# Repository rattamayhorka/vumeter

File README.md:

# Vumeter - Tablero con Control de Volumen y Display OLED multimedia 

Vumeter, es un proyecto con el que puedes mostrar en un OLED, información en tiempo real como Artista y Cancíón que se está reproduciendo en Linux, muy parecido a lo que era LCD Smartie, :D

Este script de Python interactúa con reproductores multimedia a traves de D-Bus y formatea la información y la envía al atmega32 que controla la pantalla OLED.

## Por implementar:

- vumetro (30%)
- notificaciónes (0%)

## Software

- [Python 3.x](https://www.python.org/downloads/)
- [Daemonize](https://pypi.org/project/daemonize/)
- [pydbus](https://pypi.org/project/pydbus/)
- [unidecode](https://pypi.org/project/Unidecode/)
- [pamixer](https://man.archlinux.org/man/pamixer.1)
- [playerctld](https://archlinux.org/packages/extra/x86_64/playerctl/)

## Hardware

- NEW-HEAVEN OLED DISPLAY [NHD-0420CW OLED SLIM DISPLAY] (https://newhavendisplay.com/content/specs/NHD-0420CW-AY3.pdf)
- MICROCHIP ATMEGA-32 MICROCONTROLLER [ATMEGA32](https://ww1.microchip.com/downloads/en/DeviceDoc/doc2503.pdf)
- USB SERIAL CONVERTER [USB - SERIAL TTL ](https://www.tostatronic.com/product/convertidor-ttl-pl2303-usb-to-rs232-ttl-converter/?gad_source=1&gclid=Cj0KCQiA67CrBhC1ARIsACKAa8TZjBnonuWXY4yLTC7wkeTdMWY1l-ocxSXjfy_Q063HC-wARc6UHUAaAhSuEALw_wcB)

## Conexiones: 

#define SCL PB6  
#define SDI PB5  
#define CS PB1  

## Serial interface NHD-0420CW configuration:
BS0 - GND  
BS1 - GND  
BS2 - GND  

## OLED CONNECTIONS  PCB / ATMEGA CONNECTIONS   
1  - VSS              GND  
2  - VDD              VOLTAGE  
3  - REGVDD           VOLTAGE  
4  - D/C              GND  
5  - R/W              GND  
6  - E                GND  
7  - D0 [SCLK]        PB6  
8  - D1 [SDI]         PB5  
9  - D2               GND  
10 - D3               GND  
11 - D4               GND  
12 - D5               GND  
13 - D6               GND  
14 - D7               GND  
15 - CS               PB1  
16 - RES              VOLTAGE  
17 - BS0 [SERIAL]     GND  
18 - BS1 [SERIAL]     GND  
19 - BS2 [SERIAL]     GND  
20 - VSS(FRAMEGROUND) GND

## ENCODER CONNECTIONS / ATMEGA CONNECTIONS   
1  - GND              GND  
2  - VCC              VOLTAGE  
3  - SW               PD4  
4  - DT               PD3  
5  - CLK              PD2  

## Diagrama 

## PCB 

## 3D image 

## Configuración

Asegúrate de tener todos los requisitos instalados antes de ejecutar el script.

```bash
pip install pydbus unidecode
```
## Uso

Ejecuta el script de la siguiente manera:

```bash
python dbus_data_tx.py
```

El script detectará reproductores multimedia activos y mostrará información sobre la canción en el display OLED. También permite ajustar el volumen mediante un convertidor usb-serial conectado al microcontrolador.

## Notas

- Asegúrate de tener permisos para acceder al puerto serie (`/dev/ttyUSB0` en este caso).
- Ajusta el puerto serie y el baudrate según tu configuración.

## Contribuciones

¡Contribuciones son bienvenidas! Si encuentras errores o mejoras posibles, no dudes en crear un *issue* o enviar un *pull request*.

## Autor

[rattamayhorka]

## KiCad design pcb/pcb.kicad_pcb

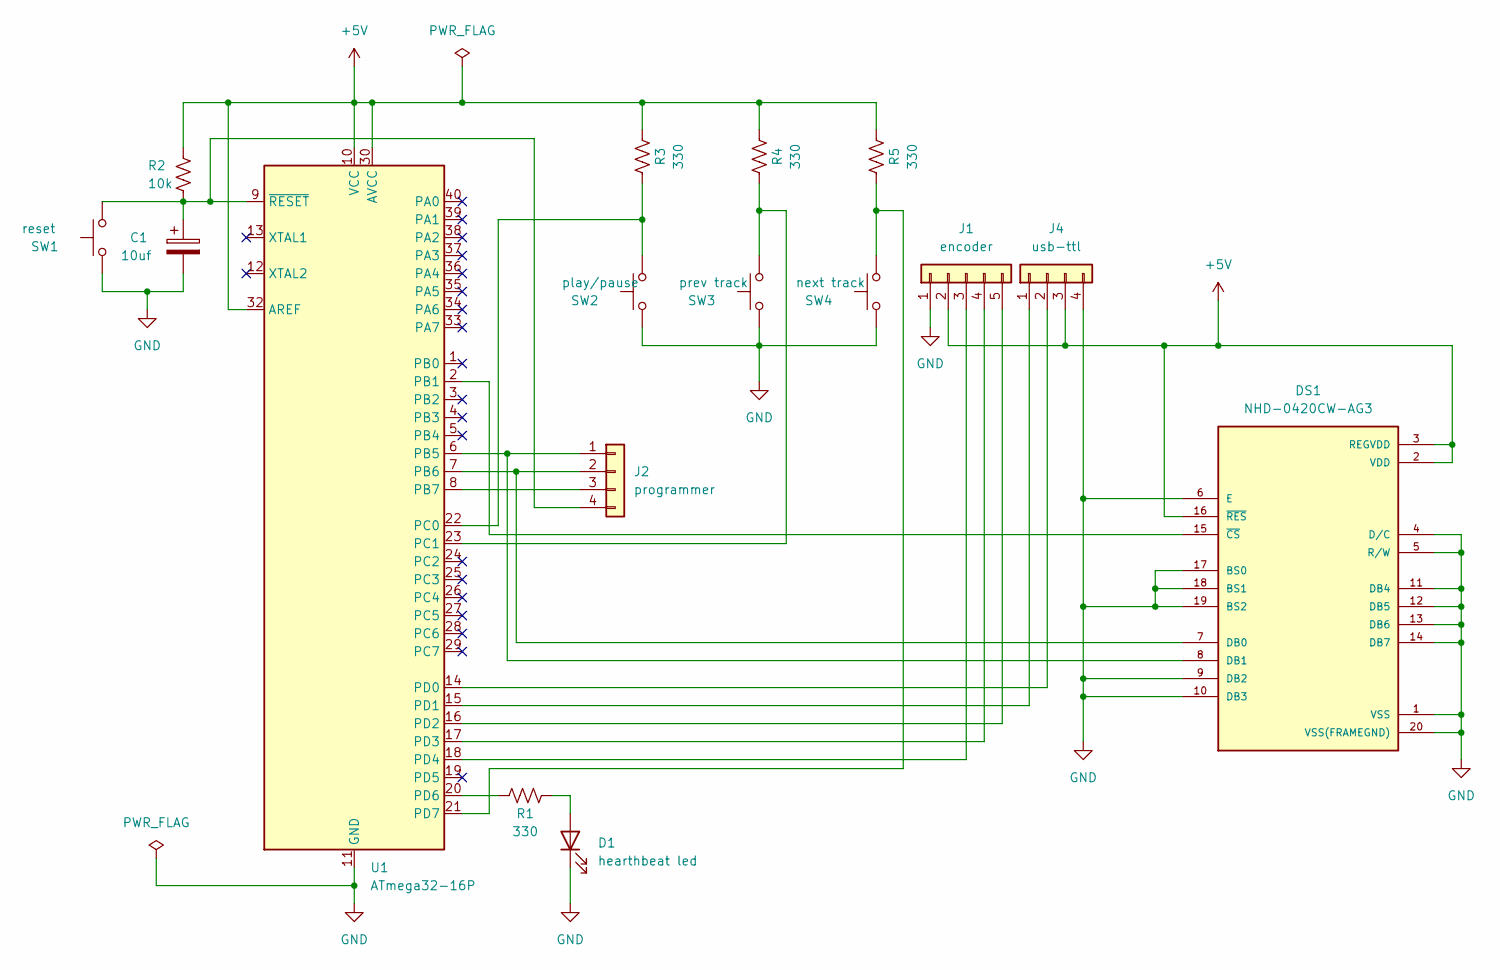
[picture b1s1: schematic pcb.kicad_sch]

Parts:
C1: 10uf; CP_Radial_D5.0mm_P2.00mm
D1: hearthbeat led; LED_D5.0mm
DS1: NHD-0420CW-AG3; NHD_NHD-0420CW-AG3
J1: encoder
J2: programmer; PinHeader_1x04_P2.54mm_Vertical
J4: usb-ttl; PinHeader_1x04_P2.54mm_Vertical
R1, R3, R4, R5: 330; R_Axial_DIN0207_L6.3mm_D2.5mm_P7.62mm_Horizontal
R2: 10k; R_Axial_DIN0207_L6.3mm_D2.5mm_P7.62mm_Horizontal
SW1: reset; SW_PUSH_6mm
SW2: play/pause; SW_PUSH_6mm
SW3: prev track; SW_PUSH_6mm
SW4: next track; SW_PUSH_6mm
U1: ATmega32-16P; DIP-40_W15.24mm

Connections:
+5V: DS1.2 (VDD), DS1.3 (REGVDD), DS1.16 (~RES), J1.2, J4.3, R2.2, R3.2, R4.2, R5.2, U1.10 (VCC), U1.30 (AVCC), U1.32 (AREF)
GND: C1.2, D1.1 (K), DS1.1 (VSS), DS1.4 (D/C), DS1.5 (R/W), DS1.6 (E), DS1.9 (DB2), DS1.10 (DB3), DS1.11 (DB4), DS1.12 (DB5), DS1.13 (DB6), DS1.14 (DB7), DS1.17 (BS0), DS1.18 (BS1), DS1.19 (BS2), DS1.20 (VSS(FRAMEGND)), J1.1, J4.4, SW1.1, SW2.1, SW3.1, SW4.1, U1.11 (GND), U1.31 (GND)
unnamed: D1.2 (A), R1.2
unnamed: DS1.7 (DB0), J2.2, U1.7 (PB6)
unnamed: DS1.8 (DB1), J2.1, U1.6 (PB5)
unnamed: DS1.15 (~CS), U1.2 (PB1)
unnamed: J1.3, U1.18 (PD4)
unnamed: J1.4, U1.17 (PD3)
unnamed: J1.5, U1.16 (PD2)
unnamed: J2.3, U1.8 (PB7)
unnamed: C1.1, J2.4, R2.1, SW1.2, U1.9 (~RESET)
unnamed: J4.1, U1.15 (PD1)
unnamed: J4.2, U1.14 (PD0)
unnamed: R3.1, SW2.2, U1.22 (PC0)
unnamed: R4.1, SW3.2, U1.23 (PC1)
unnamed: R1.1, U1.20 (PD6)
unnamed: R5.1, SW4.2, U1.21 (PD7)

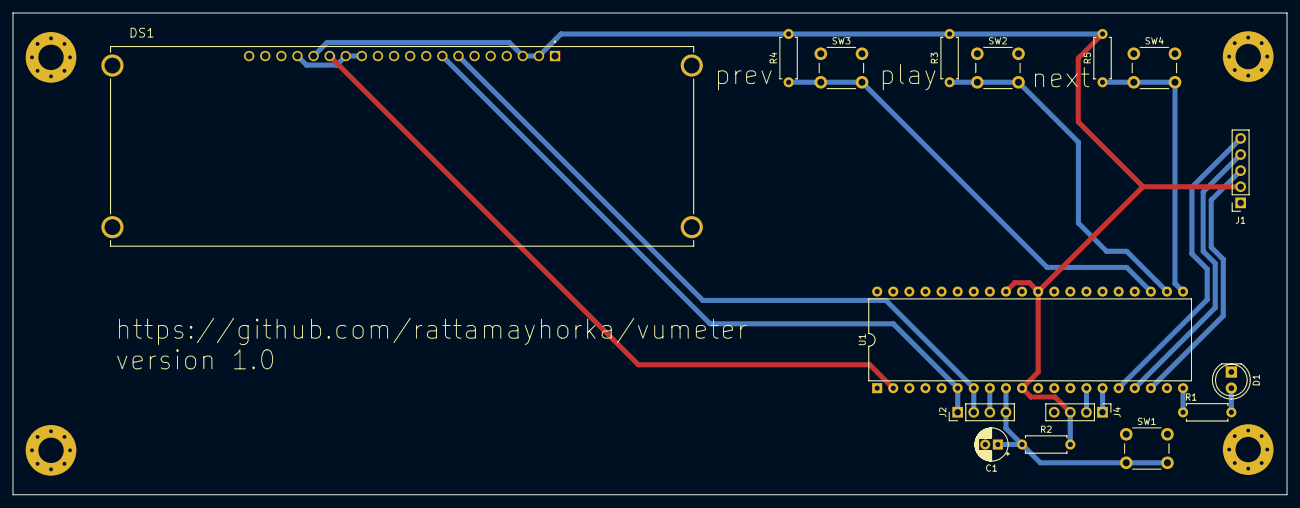
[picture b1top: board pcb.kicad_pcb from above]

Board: 2 copper layers, 201.0 x 76.0 mm, 16 parts (0 on the bottom side), 17 nets.

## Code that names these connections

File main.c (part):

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int aLastState_1;

int read_encoder(void){
    return ((PIND & (1 << PD2)) >> PD2) | (((PIND & (1 << PD3)) >> PD3) << 1);
}

void usart_init(void){
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    static uint16_t counter = 0;

    if (counter < 1) {
        PORTD |= (1 << PD6); // Enciende el LED
    } else {
        PORTD &= ~(1 << PD6); // Apaga el LED
    }

    counter++;
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}    

void ports_init(void){
    DDRB |= (1 << PB6) | (1 << PB5) | (1 << PB1); //configurar PB1 as CS, PB5 [oled 8] as SDI, pb6 as SCL [oled 7] 

    DDRD |= (1 << PD6); //configurar PD6 como salida LED heartbeat
        
    DDRC &= ~(1 << PD7); // botones multimedia (play)
    DDRC &= ~(1 << PC0); // botones multimedia (next)
    DDRC &= ~(1 << PC1); // botones multimedia (prev)

    DDRD &= ~(1 << PD4);  // PD4 como entrada (SW - encoder)
    DDRD &= ~(1 << PD3);  // PD3 como entrada (DT - encoder)
    DDRD &= ~(1 << PD2);  // PD2 como entrada (CLK - encoder)

    PORTD |= (1 << PD2) | (1 << PD3);  // Habilitar resistencias de pull-up
}

void boot(void){ //funcion de inicio
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    //boot_splash();
    usart_init(); // Inicializar USART    
    sei();
    PORTD |= (1 << PD6);    
}

int main(void){
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        }

        aLastState_1 = aState_1;
        if (!(PINC & (1 << PC0))) {
            if (switch_next == 0) {
                // El estado del interruptor ha cambiado a presionado
                char debug_message[20];
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            switch_next = 0;
        }

        if (!(PINC & (1 << PC1))) {
            if (switch_prev == 0) {
                // El estado del interruptor ha cambiado a presionado
                char debug_message[20];
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            switch_prev = 0;
        }

        if (!(PIND & (1 << PD4))) {
            if (switch_mute == 0) {
                // El estado del interruptor ha cambiado a presionado
                char debug_message[20];
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            switch_mute = 0;
        }

        if (!(PIND & (1 << PD7))) {
            if (switch_play == 0) {
                // El estado del interruptor ha cambiado a presionado
                char debug_message[20];
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
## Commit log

2023-08-20 inicio de proyecto
2023-08-23 previo a la implementación del ADC
2023-08-23 pruebas con barras y adc
2023-09-01 se actualiza el software para un lcd de 4 lineas y se corrigen caracteres
2023-09-04 modifico pines de lcd.h
2023-09-04 elimino warnings en read_adc
2023-09-05 agrego comunicacion avr@pc USART
2023-09-06 agrego los saltos de linea
2023-09-06 envío de caracteres con valor de ADC a python
2023-09-06 haciendo pruebas con control de volumen
2023-09-10 control analogico de volumen funcionando
2023-09-12 agrego opcion de salida de musica con cmus
2023-09-12 renombrar archivos
2023-09-14 separación de implementaciones
2023-09-14 limpiando versiones
2023-09-15 lcd originales de pfleury
2023-09-17 implementación de vector usart para la recepcion con interrupciones
2023-09-18 actualizando lista de archivos
2023-09-18 elimino decimales en volumen y lo envío solo si es diferente al valor enviado anterior
2023-09-20 transmision y recepcion en el mismo programa python
2023-09-21 ordenando y comentando codigo
2023-09-21 acomodando info en LCD
2023-09-21 acomodando datos en LCD
2023-09-24 agrego comandos de inicio y final de mensaje
2023-09-24 corte
2023-09-24 decodificando caracteres unicode
2023-09-25 guardo en string todo lo que llegue antes de \n
2023-09-25 actualizando a dos lineas
2023-09-26 cada que llega un nuevo mensaje \n, se guarda en un buffer diferente
2023-10-12 implementación OLED
2023-10-15 add pcb
2023-10-17 agrego 4ta linea con el dato del año
2023-10-17 agregando datos de variables de pc
2023-10-17 agrego variables de pc
2023-10-21 agrego manejo de dbus para videos de youtube
2023-10-21 implementación de notificaciones en dbus
2023-10-22 convierto caracteres a unicode
2023-10-22 agrego scroll to left
2023-10-22 implementacion de scrolling
2023-10-26 implementando scroll cadenas grandes
2023-10-27 agrego implementacion de strings mayores a 20 caracteres
2023-10-27 manejo por dbus toda la información
2023-10-28 agrego variable artist en la busqueda de youtube
2023-10-28 agrego a dbus artista
2023-10-28 elimino bugs
2023-11-03 actualizo información para trabajar con librería pydbus
2023-11-04 control de datos
2023-11-05 agrego opcion de waiting... mientras no hay reproductores activos
2023-11-05 verifico si hay información en title para soporte con bandcamp
2023-11-05 manda información solo cuando cambió de valores
2023-11-05 agrego manejo de reproductor activo como variable
2023-11-05 agrego reproductor mas legible
2023-11-08 agrego manejo de status de conexion y desconexion
2023-11-11 add split ' - ' artist and title
2023-11-12 correccion de typos
2023-11-12 enchulando en readme
2023-11-12 enchulando el readme
2023-11-18 add boot splash
2023-11-19 cambio led de status de PB0 a PD6
2023-11-20 reconfigurando despues de una perdida de fuses
2023-11-20 agrego por default la configuración de fuses de clock interno del atmega
2023-11-21 agrego pantalla de variables de PC
2023-11-21 actualizo archivos
2023-11-22 intento acoplar pc vars y dbus data
2023-11-24 borrando basura
2023-11-26 junto las pc_vars y dbus_data por tiempos
2023-11-26 pequeños cambios
2023-11-29 change adc for encoder
2023-11-29 correcion de bugs
2023-12-01 change increments for volume value
2023-12-03 actualizo archivos para pcb
2023-12-03 add connections
2023-12-03 actualizo circuito
2023-12-05 actualización de archivos pcb
2023-12-05 actualizando archivos pcb
2023-12-13 actualizo manejo de variables y tiempos en programación
2023-12-15 actualizo PCB con switches next, prev, play
2023-12-15 actualizacion de pcb
2023-12-15 add circuito
2023-12-17 haciendo pruebas con bug
2023-12-18 actualizo funciones de scrolling en oled
2023-12-18 implemento el scrolling desde python y no en el microcontrolador
2023-12-19 correccion de muestreo de variables menores de 20 chars
2023-12-19 change cmus media control to playerctl global media control
2023-12-19 add playerctl to requirements in readme.md
2023-12-19 agrego imagenes
2023-12-19 update error handling
2024-01-11 mejorando tiempos del hearthbeat castroso
2024-01-18 add oled footprint
2024-01-22 actualizacion de archivos con footprint OLED
2024-01-22 actualizacion de archivos en carpeta source
2024-01-30 actualizacion de manejo de errores
2024-02-06 add playing status on line1
2024-02-06 correcciones de impresion de caracteres
2024-02-06 corrigiendo caracteres
2024-02-08 daemonize python script
2024-02-09 agrego logging funcional
2024-02-10 daemonize con logging funcionando
2024-02-10 agrego timelapses a los mensajes del log
2024-02-10 update pcb
2024-02-18 agrego timer de apagado si no hay conexion a pc
2024-02-18 limpio variables inutilizables
2024-02-18 actualizo lista de caracteres codificados
2024-05-01 retomando proyecto
2024-05-01 add play/pause text
2024-05-02 final
2024-07-11 fix misplaced buttons (play/next)
2024-11-04 agrego identificador de usb
2024-11-04 add capavility to show cover on lcd with lcd ili9341
2024-11-24 manejo de imagen mpris sino encuentra en last.fm
2024-11-25 search last.fm cover or youtube tumbnail cover
2024-12-19 improve cover handle
2025-01-03 add lcd cover handler
2025-01-27 modificacion de rotacion por cambio de hardware
2025-02-02 actualizo lcd para mostrar vumeter simulado
2025-02-10 add image
2025-02-16 rename pcb to hardware
2025-02-16 add mic diagram for vumeter
2025-02-16 renamed files
2025-02-16 organizacion de archivos
2025-02-16 add mic amplifier circuit
2026-03-16 mejoro colores y funcionamiento de vumetro
